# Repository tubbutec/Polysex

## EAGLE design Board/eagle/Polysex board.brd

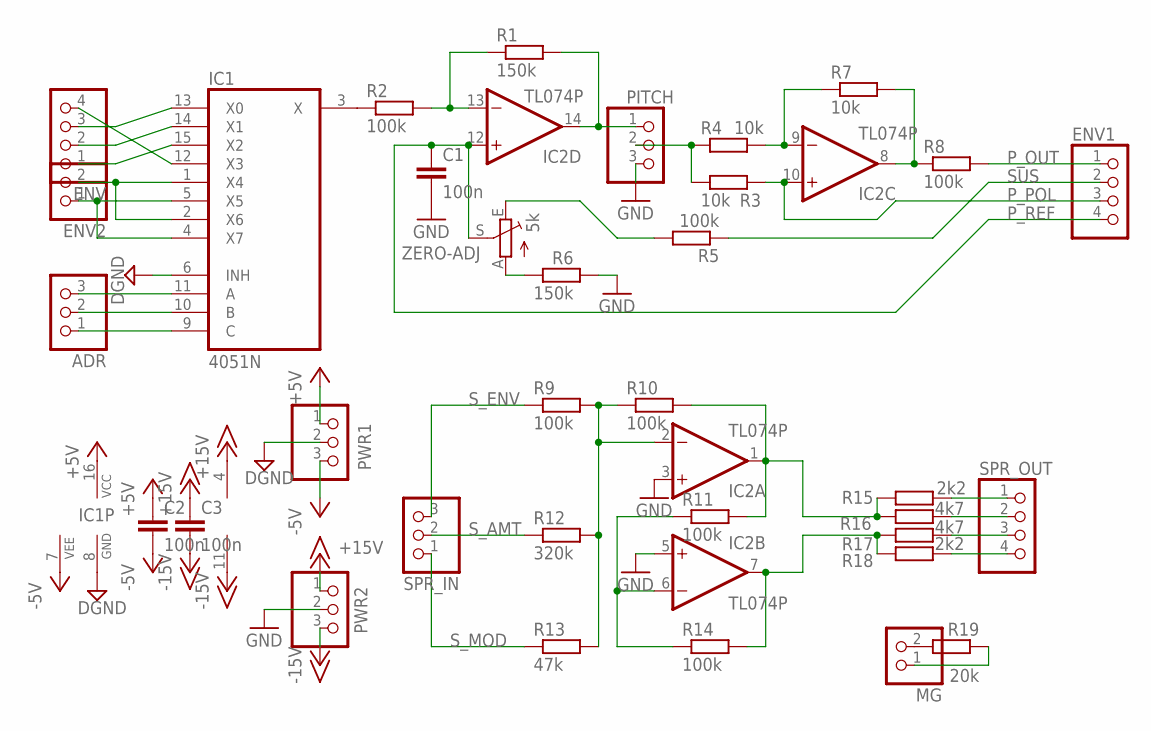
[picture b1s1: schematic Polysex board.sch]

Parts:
ADR: PINHD-1X3; 1X03
C1, C2, C3: 100n; C025-025X050
ENV, ENV1: PINHD-1X4; 1X04
ENV2: PINHD-1X2; 1X02
IC1: 4051N; DIL16
IC2: TL074P; DIL14
MG: PINHD-1X2; 1X02
PITCH: PINHD-1X3; 1X03
PWR1, PWR2: PINHD-1X3; 1X03
R1, R6: 150k; 0204/7
R2, R5, R8, R9, R10, R11, R14: 100k; 0204/7
R3, R4, R7: 10k; 0204/7
R12: 320k; 0204/7
R13: 47k; 0204/7
R15, R18: 2k2; 0204/7
R16, R17: 4k7; 0204/7
R19: 20k; 0204/7
SPR_IN: PINHD-1X3; 1X03
SPR_OUT: PINHD-1X4; 1X04
ZERO-ADJ: 5k; CA6V

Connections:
+5V: C2.1, IC1.16 (VCC), PWR1.1
+15V: C3.1, IC2.4 (V+), PWR2.1
-5V: C2.2, IC1.7 (VEE), PWR1.3
-15V: C3.2, IC2.11 (V-), PWR2.3
DGND: IC1.6 (INH), IC1.8 (GND), PWR1.2
GND: C1.2, IC2.3 (+IN), IC2.5 (+IN), PITCH.3, PWR2.2, R6.2
unnamed: IC1.3 (X), R2.1
unnamed: IC2.13 (-IN), R1.1, R2.2
unnamed: IC2.14 (OUT), PITCH.1, R1.2
unnamed: R5.2, ZERO-ADJ.E
unnamed: MG.2, R19.1
unnamed: IC2.9 (-IN), R4.2, R7.1
unnamed: MG.1, R19.2
unnamed: PITCH.2, R3.1, R4.1
unnamed: IC2.8 (OUT), R7.2, R8.1
unnamed: R6.1, ZERO-ADJ.A
unnamed: IC2.2 (-IN), R9.2, R10.1, R12.2, R13.2
unnamed: IC2.1 (OUT), R10.2, R11.2, R15.1, R16.1
unnamed: IC2.6 (-IN), R11.1, R14.1
unnamed: IC2.7 (OUT), R14.2, R17.1, R18.1
unnamed: R15.2, SPR_OUT.1
unnamed: R16.2, SPR_OUT.2
unnamed: R17.2, SPR_OUT.3
unnamed: R18.2, SPR_OUT.4
unnamed: ADR.1, IC1.9 (C)
unnamed: ADR.2, IC1.10 (B)
unnamed: ADR.3, IC1.11 (A)
P_OUT: ENV1.1, R8.2
P_POL: ENV1.3, IC2.10 (+IN), R3.2
P_REF: C1.1, ENV1.4, IC2.12 (+IN), ZERO-ADJ.S
SUS: ENV1.2, R5.1
S_AMT: R12.1, SPR_IN.2
S_ENV: R9.1, SPR_IN.3
S_MOD: R13.1, SPR_IN.1
X0: ENV.3, IC1.13 (X0)
X1: ENV.2, IC1.14 (X1)
X2: ENV.1, IC1.15 (X2)
X3: ENV.4, IC1.12 (X3)
X4: ENV2.2, IC1.1 (X4), IC1.2 (X6)
X5: ENV2.1, IC1.4 (X7), IC1.5 (X5)

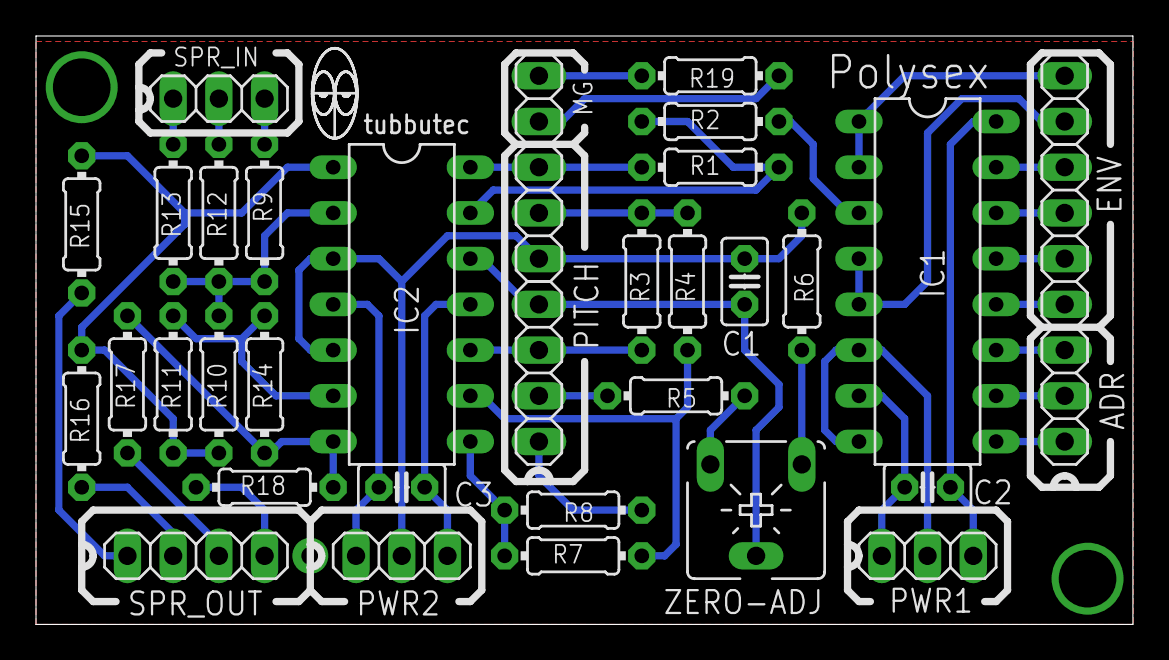
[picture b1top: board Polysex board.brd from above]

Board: 2 copper layers, 60.9 x 32.7 mm, 35 parts (0 on the bottom side), 40 nets.

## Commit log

2024-06-12 added PCB version by Ewan Colsell

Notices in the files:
Board/eagle/Polysex board.brd:
Copyright Tobias Münzer, Tubbutec 2016.
This  documentation  describes  Open  Hardware  and  is  licensed  under  the
CERN OHL v. 1.2.
